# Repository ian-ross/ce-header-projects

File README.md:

# Projects using Contextual Electronics header

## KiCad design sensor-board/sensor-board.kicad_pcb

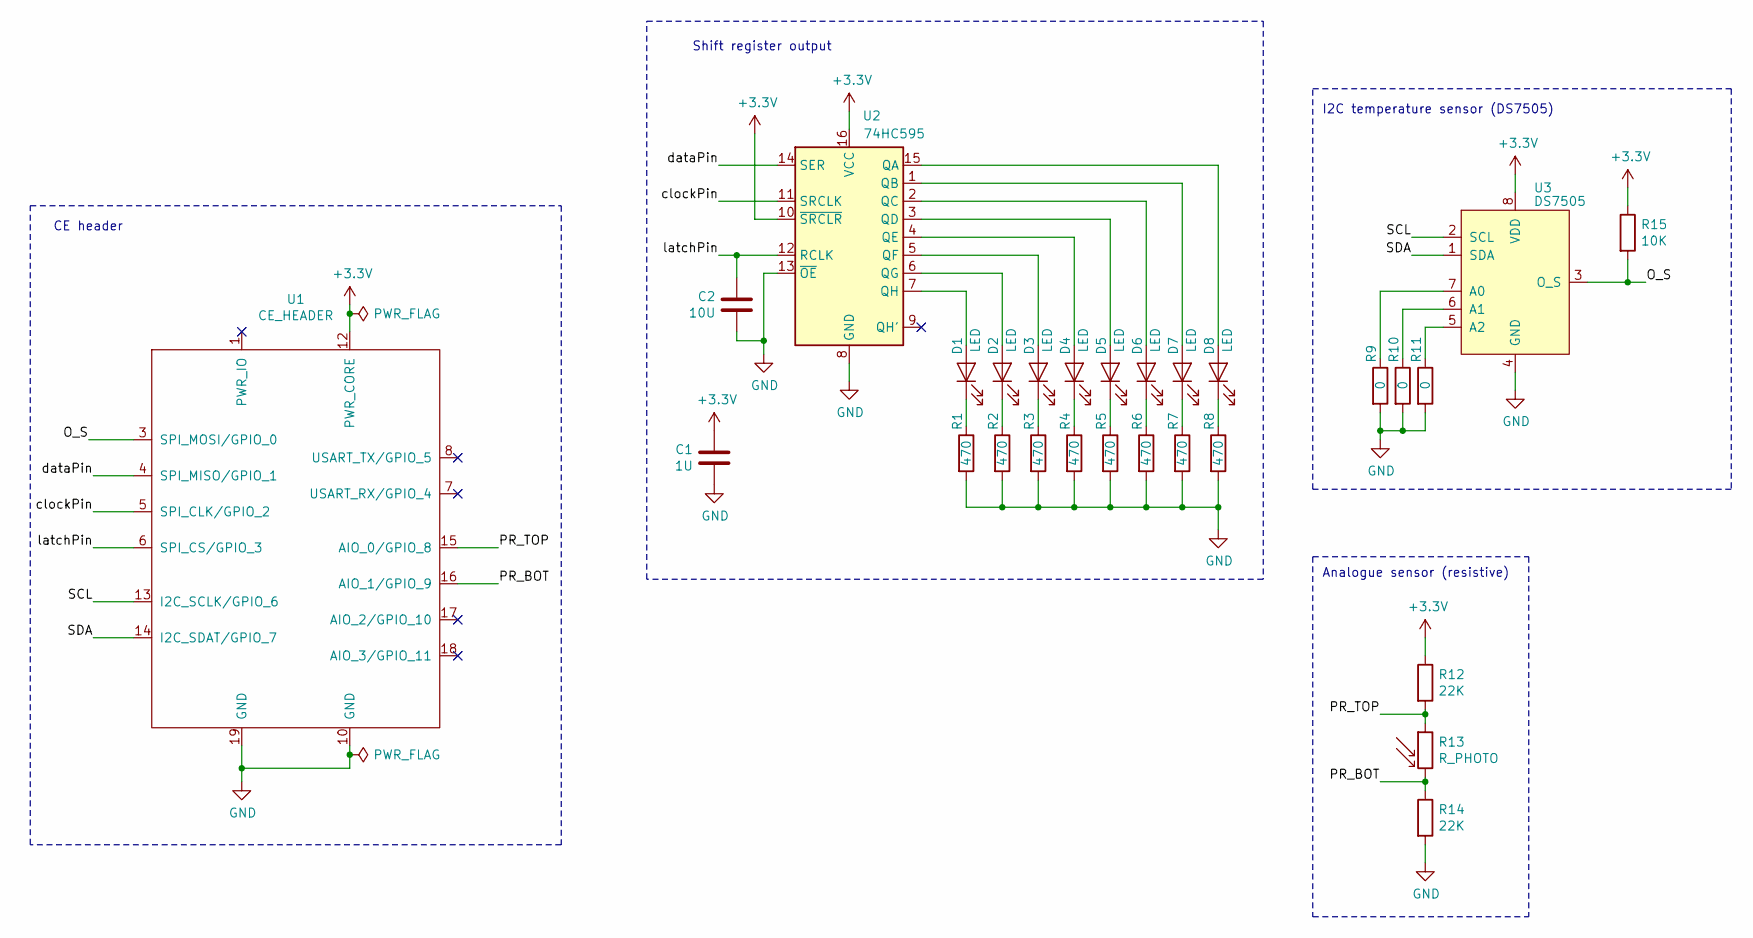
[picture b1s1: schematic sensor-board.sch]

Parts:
C1: 1U; C_0805_2012Metric
C2: 10U; C_0805_2012Metric
D1, D2, D3, D4, D5, D6, D7, D8: LED; LED_0805_2012Metric; MPN 150080RS75000
R1, R2, R3, R4, R5, R6, R7, R8: 470; R_0805_2012Metric
R9, R10, R11: 0; R_0805_2012Metric
R12, R14: 22K; R_0805_2012Metric
R13: R_PHOTO; R_LDR_5.1x4.3mm_P3.4mm_Vertical; MPN PDV-P8103
R15: 10K; R_0805_2012Metric
U1: CE_HEADER; CE_Header
U2: 74HC595; SOIC-16_3.9x9.9mm_P1.27mm
U3: DS7505; SOIC-8_3.9x4.9mm_P1.27mm

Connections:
+3V3: C1.2, R12.1, R15.1, U1.12 (PWR_CORE), U2.10 (~SRCLR), U2.16 (VCC), U3.8 (VDD)
/O_S: R15.2, U1.3 (SPI_MOSI/GPIO_0), U3.3 (O_S)
/PR_BOT: R13.2, R14.1, U1.16 (AIO_1/GPIO_9)
/PR_TOP: R12.2, R13.1, U1.15 (AIO_0/GPIO_8)
/SCL: U1.13 (I2C_SCLK/GPIO_6), U3.2 (SCL)
/SDA: U1.14 (I2C_SDAT/GPIO_7), U3.1 (SDA)
/clockPin: U1.5 (SPI_CLK/GPIO_2), U2.11 (SRCLK)
/dataPin: U1.4 (SPI_MISO/GPIO_1), U2.14 (SER)
/latchPin: C2.2, U1.6 (SPI_CS/GPIO_3), U2.12 (RCLK)
GND: C1.1, C2.1, R1.2, R2.2, R3.2, R4.2, R5.2, R6.2, R7.2, R8.2, R9.2, R10.2, R11.2, R14.2, U1.10 (GND), U1.19 (GND), U2.8 (GND), U2.13 (~OE), U3.4 (GND)
unnamed: D1.1 (K), R1.1
unnamed: D1.2 (A), U2.7 (QH)
unnamed: D2.1 (K), R2.1
unnamed: D2.2 (A), U2.6 (QG)
unnamed: D3.1 (K), R3.1
unnamed: D3.2 (A), U2.5 (QF)
unnamed: D4.1 (K), R4.1
unnamed: D4.2 (A), U2.4 (QE)
unnamed: D5.1 (K), R5.1
unnamed: D5.2 (A), U2.3 (QD)
unnamed: D6.1 (K), R6.1
unnamed: D6.2 (A), U2.2 (QC)
unnamed: D7.1 (K), R7.1
unnamed: D7.2 (A), U2.1 (QB)
unnamed: D8.1 (K), R8.1
unnamed: D8.2 (A), U2.15 (QA)
unnamed: R9.1, U3.7 (A0)
unnamed: R10.1, U3.6 (A1)
unnamed: R11.1, U3.5 (A2)

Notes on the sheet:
Analogue sensor (resistive)
I2C temperature sensor (DS7505)
CE header
Shift register output

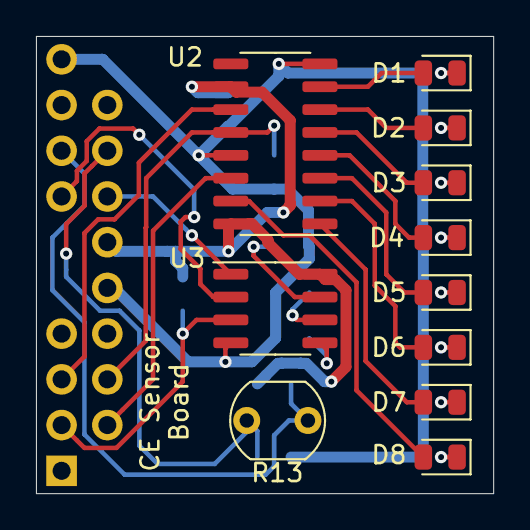
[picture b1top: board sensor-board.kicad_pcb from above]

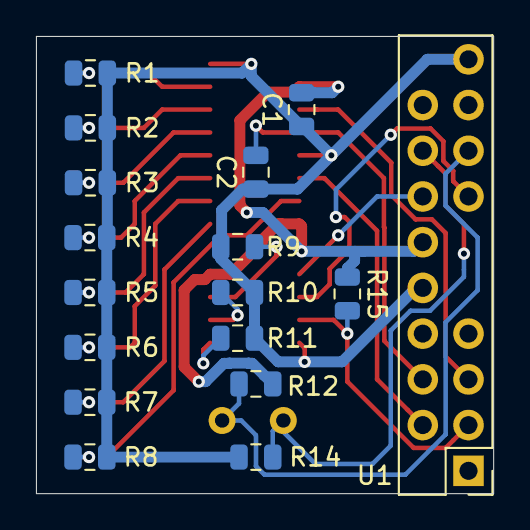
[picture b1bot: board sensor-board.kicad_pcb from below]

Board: 2 copper layers, 25.4 x 25.4 mm, 28 parts (17 on the bottom side), 29 nets.

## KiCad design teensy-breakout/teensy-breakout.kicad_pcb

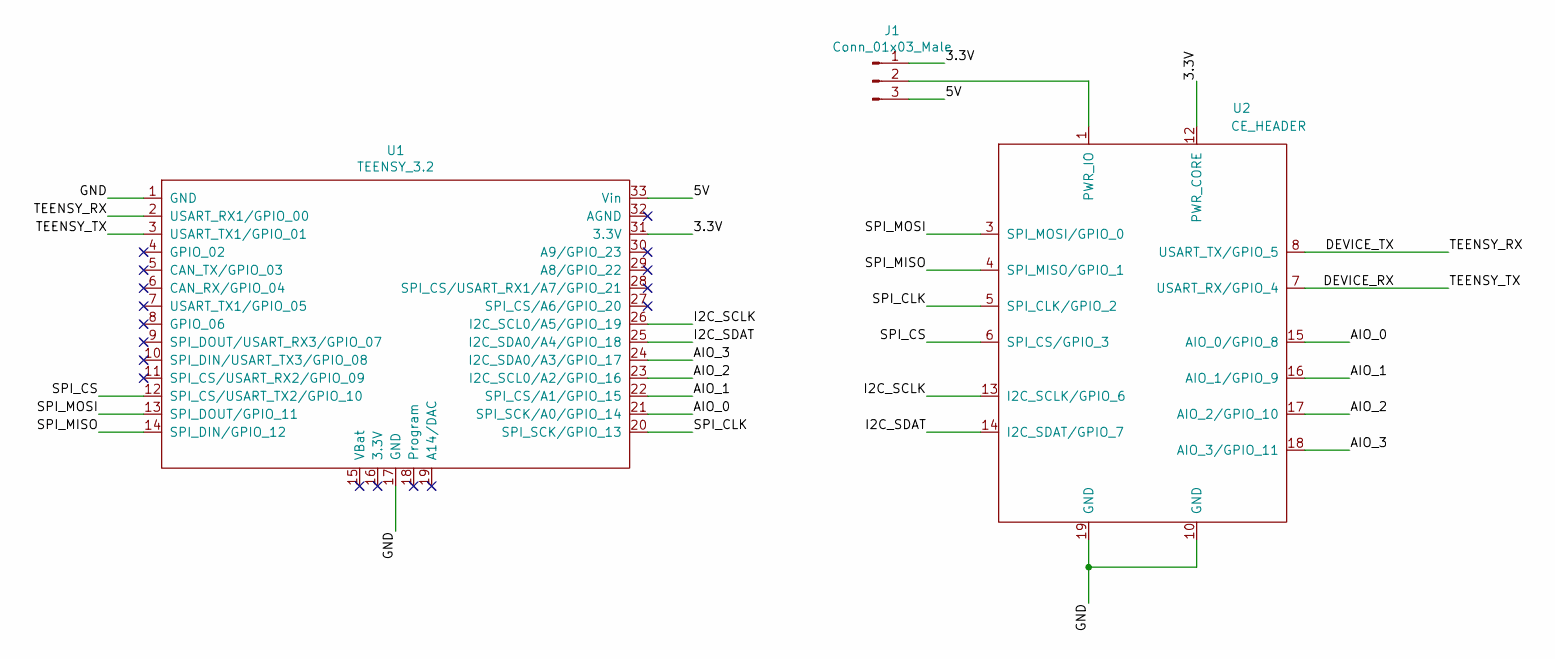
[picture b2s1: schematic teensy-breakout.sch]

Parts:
J1: Conn_01x03_Male; PinHeader_1x03_P2.54mm_Vertical
U1: TEENSY_3.2
U2: CE_HEADER; CE_Header_Converter

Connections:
/3.3V: J1.1, U1.31 (3.3V), U2.12 (PWR_CORE)
/5V: J1.3, U1.33 (Vin)
/AIO_0: U1.21 (SPI_SCK/A0/GPIO_14), U2.15 (AIO_0/GPIO_8)
/AIO_1: U1.22 (SPI_CS/A1/GPIO_15), U2.16 (AIO_1/GPIO_9)
/AIO_2: U1.23 (I2C_SCL0/A2/GPIO_16), U2.17 (AIO_2/GPIO_10)
/AIO_3: U1.24 (I2C_SDA0/A3/GPIO_17), U2.18 (AIO_3/GPIO_11)
/DEVICE_RX: U1.3 (USART_TX1/GPIO_01), U2.7 (USART_RX/GPIO_4)
/DEVICE_TX: U1.2 (USART_RX1/GPIO_00), U2.8 (USART_TX/GPIO_5)
/GND: U1.1 (GND), U1.17 (GND), U2.10 (GND), U2.19 (GND)
/I2C_SCLK: U1.26 (I2C_SCL0/A5/GPIO_19), U2.13 (I2C_SCLK/GPIO_6)
/I2C_SDAT: U1.25 (I2C_SDA0/A4/GPIO_18), U2.14 (I2C_SDAT/GPIO_7)
/SPI_CLK: U1.20 (SPI_SCK/GPIO_13), U2.5 (SPI_CLK/GPIO_2)
/SPI_CS: U1.12 (SPI_CS/USART_TX2/GPIO_10), U2.6 (SPI_CS/GPIO_3)
/SPI_MISO: U1.14 (SPI_DIN/GPIO_12), U2.4 (SPI_MISO/GPIO_1)
/SPI_MOSI: U1.13 (SPI_DOUT/GPIO_11), U2.3 (SPI_MOSI/GPIO_0)
unnamed: J1.2, U2.1 (PWR_IO)

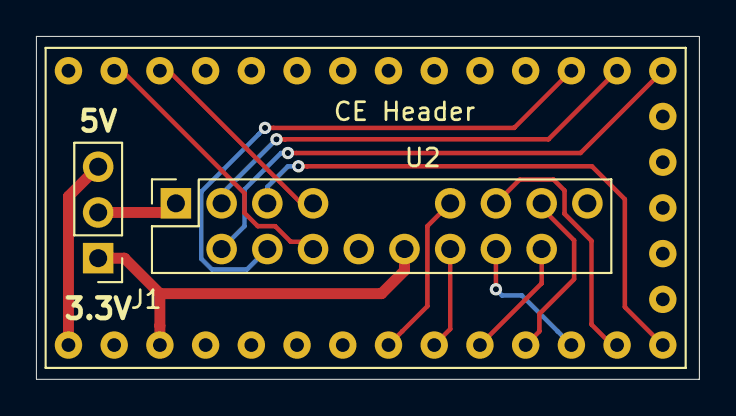
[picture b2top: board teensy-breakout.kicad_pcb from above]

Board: 2 copper layers, 36.8 x 19.0 mm, 3 parts (0 on the bottom side), 16 nets.

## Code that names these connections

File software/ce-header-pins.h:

#ifndef _H_CE_HEADER_PINS_
#define _H_CE_HEADER_PINS_

#define SPI_MOSI 11
#define GPIO_0 11

#define SPI_MISO 12
#define GPIO_1 12

#define SPI_CLK 13
#define GPIO_2 13

#define SPI_CS 10
#define GPIO_3 10

#define USART_RX 1
#define GPIO_4 1

#define USART_TX 0
#define GPIO_5 0

#define I2C_SCLK 19
#define GPIO_6 19

#define I2C_SDAT 18
#define GPIO_7 18

#define AIO_0 14
#define GPIO_8 14

#define AIO_1 15
#define GPIO_9 15

#define AIO_2 16
#define GPIO_10 16

#define AIO_3 17
#define GPIO_11 17

#endif

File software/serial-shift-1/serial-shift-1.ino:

#include "ce-header-pins.h"

int latchPin = GPIO_3;
int clockPin = GPIO_2;
int dataPin = GPIO_1;

void setup() {
  pinMode(latchPin, OUTPUT);
  pinMode(clockPin, OUTPUT);
  pinMode(dataPin, OUTPUT);
}

void loop() {
  for (int n = 0; n < 256; n++) {
    // take the latchPin low so 
    // the LEDs don't change while you're sending in bits:
    digitalWrite(latchPin, LOW);
    // shift out the bits:
    shiftOut(dataPin, clockPin, MSBFIRST, n);  

    //take the latch pin high so the LEDs will light up:
    digitalWrite(latchPin, HIGH);
    // pause before next value:
    delay(500);
  }
}

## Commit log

2020-02-08 Initial setup: CE header and start of Teensy breakout
2020-02-08 Connected Teensy breakout to CE header
2020-02-08 Teensy breakout board
2020-02-08 Production data for Teensy breakout board
2020-02-08 Sensor board schematic and first attempt at layout
2020-03-15 Finishing off Teensy project
2020-03-25 Add software for light and temperature data collection
